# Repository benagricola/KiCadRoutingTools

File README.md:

# KiCad Routing Tools

A fast Rust-accelerated A* autorouter for KiCad PCB files. Compatible with **KiCad 9 and KiCad 10**. Available as both a **KiCad Plugin** with full GUI and a **Command-Line Interface** for scripting and automation.

📊 **[Project metrics](https://drandyhaas.github.io/KiCadRoutingTools/metrics/)** — installs, downloads and traffic, updated daily.

☕ **[Donate](https://ko-fi.com/drandyhaas)** — the tool is free and MIT-licensed; donations cover the ~$500/month of cloud compute and AI development behind it.

## Contents

- [Features](#features)
- [Quick Start](#quick-start)
- [KiCad Plugin](#kicad-plugin) — GUI, the AI **AI tab**, installation
- [Command-Line Interface](#command-line-interface) — routing, planes, verification
- [Documentation](#documentation) — full guide for every feature
- [Project Structure](#project-structure) & [Module Overview](#module-overview)
- [Performance](#performance)
- [Command Reference](#command-reference) — options per tool (full list: `--help` / [configuration.md](docs/configuration.md))
- [Project metrics](https://drandyhaas.github.io/KiCadRoutingTools/metrics/) — installs, downloads and traffic
- [Requirements](#requirements) · [Limitations](#limitations) · [Contributing](#contributing) · [Support](#support) · [License](#license)

## Features

Fast, grid-based A\* routing with a native Rust core (~10× faster than pure Python): octilinear (H/V/45°) multi-layer routing with automatic vias, and batch routing with incremental obstacle caching. Highlights below link to the full deep-dive docs.

**Core routing**
- Rust-accelerated A\* pathfinding, multi-layer with automatic via insertion
- [Rip-up and reroute](docs/rip-up-reroute.md) — progressive N+1 blocker analysis, ripped-corridor avoidance
- [Net ordering strategies](docs/net-ordering.md) — MPS (crossing-aware), inside-out, or original, with MPS layer swaps
- Stub layer switching, vertical track alignment, turn-cost straightening
- Board-edge (Edge.Cuts arcs/cutouts), keep-out rule areas, and auto BGA exclusion zones — see [Configuration](docs/configuration.md)
- Direction-aware stub / BGA / track [proximity penalties](docs/configuration.md)

**Differential pairs** — see [Differential Pairs](docs/differential-pairs.md)
- Pose-based A\* with a Dubins heuristic and adaptive setback angles for orientation-aware centerlines
- Bare-pad, multi-point (3+ terminals), and hybrid (coupled middle + single-ended legs) routing
- Automatic polarity resolution (opt-in pad swaps), U-turn prevention, GND return-via placement
- Electrically-short legs auto-defer to single-ended; per-layer [impedance-controlled](docs/differential-pairs.md) widths

**Power & planes** — see [Plane Routing](docs/route-plane.md) and [Power Nets](docs/power-nets.md)
- [Wider power-net routing](docs/power-nets.md) with automatic neck-down at fine-pitch pads
- Plane pours (pads are welded by the route step, #562) and multi-net Voronoi plane layers with resistance / max-current reporting
- Disconnected-plane-region repair (region joins + pad taps) and GND return-via placement

**Signal integrity**
- [Length matching](docs/length-matching.md) — trombone meanders, auto DQ/DQS grouping, via-barrel aware
- [Time matching](docs/length-matching.md#time-matching) — propagation delay, microstrip vs stripline
- [Bus routing](docs/bus-routing.md), plus [guide corridors and keep-out zones](docs/configuration.md) drawn on a User layer

**Placement, fanout & optimization**
- [Placement optimization](docs/placement-optimization.md) for routability, before routing
- [The design brief](docs/design-brief.md) — state what the board is FOR, in a sibling the toolchain reads: which connectors are user-facing, which edge each belongs on and where along it
- [Floorplan intent, graded](docs/floorplan-intent.md) — declare where parts belong and check the board against it, so "the render looks fine" stops being a verdict
- BGA / QFN fanout with decoupling-cap placement cleanup, Hungarian target-swap, and schematic sync

**Cleanup & verification** — see [Utilities](docs/utilities.md)
- Post-route copper cleanup reconciled against the connectivity model (no orphaned or ripped-and-not-restored copper), with gap-snap connectors
- **KiCad-oracle reconnect** — routes the exact links KiCad's own DRC reports as unconnected
- Checkers for DRC, connectivity, orphan stubs, copper hygiene (`check_weird.py`), and pad geometry

**Interfaces**
- Full [KiCad plugin GUI](#kicad-plugin) (KiCad 9 & 10) and a scriptable [CLI](#command-line-interface)
- [AI assistance](docs/claude-skills.md) — a **AI tab** that plans an entire routing workflow, per-field "Ask AI" helpers, and datasheet-driven power / high-speed / diff-pair analysis
- [Board rendering & routing animation](docs/route-animation.md) — fast geometry PNG renderer, plus a movie of the router laying/ripping/restoring copper (`make_movie.py`, or the Advanced options tab's **Make routing movie** debug checkbox → `.mp4`/`.gif`)
- [Routing plans as files](docs/claude-skills.md#plans-from-the-command-line) — save/load a whole routing chain as JSON: build one from a recorded command chain (`make_plan.py`), run it headless through the real plugin (`run_plan.py`), or load it in the GUI

## Quick Start

### 1. Get the Code

```bash
# Clone with git
git clone https://github.com/drandyhaas/KiCadRoutingTools.git
cd KiCadRoutingTools
```

Or [download the ZIP](https://github.com/drandyhaas/KiCadRoutingTools/archive/refs/heads/main.zip) and extract it.

### 2. Install the Rust Router

```bash
python build_router.py
```

By default this downloads a prebuilt binary for your OS from the project's
[GitHub Releases](https://github.com/drandyhaas/KiCadRoutingTools/releases) —
**no Rust toolchain required**. Prebuilts are published for:

- Linux x86_64
- macOS arm64 (Apple Silicon)
- macOS x86_64 (Intel)
- Windows x86_64

If a prebuilt isn't available for your platform (e.g. Linux arm64) or the
download fails, the script falls back to building locally with cargo.

#### Building from source (optional)

If you'd rather build locally — or you're on a platform without a prebuilt —
install Rust from [rustup.rs](https://rustup.rs/):

```bash
# macOS / Linux
curl --proto '=https' --tlsv1.2 -sSf https://sh.rustup.rs | sh

# Windows: Download and run rustup-init.exe from https://rustup.rs/
```

After installation, restart your terminal or run `source ~/.cargo/env`, then:

```bash
python build_router.py --from-source     # build locally instead of downloading
python build_router.py --tag v0.15.0     # download a specific release
python build_router.py --clean           # remove all build artifacts
```

### 3. Choose Your Interface

**Option A: KiCad Plugin (Recommended for interactive use)**

```bash
# Install the plugin
python install_plugin.py

# Then in KiCad: Tools → External Plugins → KiCadRoutingTools
```

**Option B: Claude Code (AI-assisted routing)**

Use [Claude Code](https://claude.ai/claude-code) to analyze your PCB and generate a routing plan:

```
> /plan-pcb-routing kicad_files/my_board.kicad_pcb
```

Claude will:
- Analyze your board structure and identify components needing fanout (BGA/QFN/PGA)
- Detect differential pairs and DDR signals requiring length matching
- Identify power/ground nets and recommend plane vs trace routing
- Assess signal speeds and recommend GND return via placement
- Generate a step-by-step routing plan with explanations
- Run the commands and verify results

Other useful skills:
```
> /find-high-speed-nets kicad_files/my_board.kicad_pcb       # Identify high-speed nets via datasheet lookup
> /analyze-power-nets kicad_files/my_board.kicad_pcb         # Identify power nets and track widths
> /identify-diff-pairs kicad_files/my_board.kicad_pcb        # Find diff pairs by pin function, recommend gap/impedance
> /recommend-stackup kicad_files/my_board.kicad_pcb          # Stackup advice for impedance/time-matching accuracy
> /diagnose-routing-failures my_board.kicad_pcb /tmp/route_output.txt  # Root-cause failed routes, get a retry command
> /review-routed-board my_board_routed.kicad_pcb             # Post-route QA: DRC, connectivity, length match, GND vias
```

See [Claude Skills](docs/claude-skills.md) for what each skill does and how they fit together.

All of these are also available inside KiCad without leaving the plugin - see [AI assistance in the plugin](#ai-assistance-ai-tab) below. The plugin can run the same skills through [opencode](https://opencode.ai) instead of Claude Code (issue #503) - a Backend dropdown on the AI tab selects the agent CLI, and opencode's `provider/model` strings open the door to other model providers. The skills' output contracts are tuned on Claude models; smaller models may follow them less reliably.

**Option C: Manual Command Line (For scripting and automation)**

```bash
# Optionally optimize an existing placement for routability (before routing)
python py_placer/place_optimize.py my_board.kicad_pcb --max-displacement 3

# Pour the planes FIRST (#562): the fanout's plane-drop vias then land on
# real fill, and the route step welds plane pads into it.
python py_router/route_planes.py my_board.kicad_pcb poured.kicad_pcb --nets GND --plane-layers B.Cu

# Fan out a BGA, then tidy decoupling caps off the new vias (issue #130)
python py_router/bga_fanout.py poured.kicad_pcb -c U1 -o fanned.kicad_pcb --clearance 0.1
python py_placer/place_fanout_clearance.py fanned.kicad_pcb capclean.kicad_pcb --clearance 0.1

# Route differential pairs
python py_router/route_diff.py capclean.kicad_pcb -o diffed.kicad_pcb --nets "*lvds*"

# Route ALL remaining nets, plane nets included (their widths via --power-nets).
# This step ends with the in-run plane finalize that completes the planes.
python py_router/route.py diffed.kicad_pcb routed.kicad_pcb --nets "*" \
    --power-nets GND --power-nets-widths 0.3
```

---

## KiCad Plugin

The plugin provides a full graphical interface for all routing features, running directly within KiCad 9 or 10.

### AI assistance (AI tab)

With [Claude Code](https://claude.ai/claude-code) or [opencode](https://opencode.ai) installed, the routing dialog gains AI assistance throughout (the plugin spawns the selected agent CLI headless, streams a live transcript, and fills GUI controls from the results). The **Backend** dropdown on the AI tab picks the CLI: Claude Code runs Anthropic models; opencode takes `provider/model` strings for many providers (including its built-in free tier), with `opencode auth login` adding provider accounts. Both discover the same `.claude/skills/`; opencode runs them under a read-only `pcb-analysis` agent defined in `opencode.json` (the equivalent of the Claude run's read-only tool allowlist). Neither grants a dedicated write tool, though both grant `Bash`, so neither is a sandbox — the allowlist states intent, and `--allowedTools` auto-approves rather than restricts. They are also not identical: the Claude list grants the subagent-dispatch tool, so an analysis skill there can dispatch an independent verifier (#552), which opencode's pinned agent has no per-run equivalent for. A caller asking opencode for a tool set naming `Write`/`Edit` is refused rather than silently downgraded.

- **AI tab** - *Plan Routing* runs `/plan-pcb-routing`: the plan fills the parameter fields across the tabs and appears as a checkable step list, which *Run Selected Steps* executes sequentially in-process on the live board with per-step status marks. *Review Routed Board* and *Diagnose Routing Failures* give post-route QA and failure root-causing. Backend, model, and effort selectors control every AI run and persist with the dialog settings (model/effort remembered per backend).
- **Save / Load a plan** - *Save…* writes the generated step list to a JSON file; *Load…* reads one back and runs it with **no Claude call** — handy for replaying a workflow that worked on another board. A recorded stress-test chain converts to a loadable plan too (`tests/stress/manifest_to_plan.py <board>/redo_commands.sh plan.json`).
- **Per-field "Ask AI" buttons** - power nets/widths (Route tab), stackup check (Layers), differential-pair verification by pin function (Differential tab), net-to-plane layer mappings and GND return via distance (Planes tab).

The full button-to-skill map is in [Claude Skills - Plugin GUI Integration](docs/claude-skills.md#plugin-gui-integration). Datasheet-based skills use web lookups and take a few minutes; every run shows a live transcript with cancel.

### Installation

Three ways to install:

**A. KiCad Plugin and Content Manager (PCM)** — the recommended path for end users, and it needs no extra repository URL: the package has been in the **official KiCad repository** (the one KiCad ships with, `gitlab.com/kicad/addons`) since v0.15.6. Open the PCM from the KiCad main window, leave the repository dropdown on *KiCad official repository*, go to the **Plugins** tab, search for `routing`, select *KiCad Routing Tools* and click **Install**, then **Apply Changes** at the bottom. If it is not listed, the PCM is serving a cached catalogue — press **Refresh** and look again. Versions are published with status `testing` rather than `stable`, which the PCM shows in the Status column but does not hide or block; `kicad_version` is a *minimum*, so the 9.0 entry installs on KiCad 10 as well. On first launch, the plugin checks the Python packages listed in `requirements.txt` (`numpy`, `scipy`, `shapely`) and offers a one-click pip install for any that are missing **or too old** into KiCad's Python. Do not assume KiCad supplies them: what it bundles varies by version and platform, and KiCad 10 on macOS ships no `numpy` at all. The check reports the version and the file path the *running* interpreter imports — KiCad's Python is often not the one `pip show numpy` answers for in a terminal.

**B. PCM "Install from File…" using the release zip** — for a release newer than the one the official catalogue currently carries, for a pinned older version, or for an offline machine. Each [GitHub Release](https://github.com/drandyhaas/KiCadRoutingTools/releases) ships a ready-to-install PCM package zip named `KiCadRoutingTools-<version>.zip` (a single cross-platform archive bundling the prebuilt Rust binaries for all platforms — **not** the auto-generated "Source code (zip)"). To install it:

1. From the Release's *Assets*, download `KiCadRoutingTools-<version>.zip` (e.g. `KiCadRoutingTools-0.15.13.zip`).
2. In KiCad, open **Plugin and Content Manager** from the main window.
3. Click **Install from File…** (bottom of the PCM dialog) and select the downloaded zip.
4. Click **Apply Pending Changes**, then restart KiCad if prompted.

The plugin appears under *Tools → External Plugins* in the PCB Editor. The same first-launch `scipy`/`shapely` dependency check described in (A) applies. This path keeps the plugin manageable from the PCM (you can update or uninstall it there), unlike the manual install below.

**C. Manual install from source** — for development or for using the CLI tools as well:

```bash
# Install the plugin (copies to KiCad plugins directory)
python install_plugin.py

# For development: create symlink instead of copying
python install_plugin.py --symlink

# Remove the plugin
python install_plugin.py --uninstall
```

The installer automatically detects your KiCad installation directory (supports KiCad 9.0 and 10.0):
- **macOS**: `~/Documents/KiCad/<version>/3rdparty/plugins/`
- **Linux**: `~/.local/share/kicad/<version>/3rdparty/plugins/`
- **Windows**: `~/Documents/KiCad/<version>/3rdparty/plugins/`

The installer also installs `requirements.txt` into KiCad's Python with pip, and skips pip when that Python already has everything. On Linux, KiCad runs the system Python, which Debian 12+, Ubuntu 23.04+, Fedora 38+ and Arch mark as externally managed (PEP 668) so pip refuses to install into it; there the installer runs no pip and prints the `apt` / `dnf` / `pacman` command for whatever is missing, plus the explicit `--break-system-packages` override for a package your distribution does not carry.

If you previously installed this plugin through the Plugin & Content Manager, that copy sits next to the local install and would shadow it on `sys.path` (causing stale-code errors). The installer detects any such PCM copy and moves it aside to `<kicad-base>/disabled_pcm_plugins/<version>/`, leaving it recoverable. Pass `--keep-pcm` to skip this.

### Releasing a new version (maintainers)

The full release flow — version bump, GitHub Release, and the merge request to the official KiCad PCM repository — is documented step by step in **[docs/release-pipeline.md](docs/release-pipeline.md)**.

Short version:

1. Bump `VERSION` and the `versions[]` entry in `metadata.json`.
2. `git tag v0.15.6 && git push --tags` — CI builds all 4 platform binaries, packages a single `KiCadRoutingTools-<ver>.zip` (the PCM validator rejects duplicate version strings, so we ship one cross-platform zip), patches `metadata.json` with real sha256/size values, and attaches everything to the GitHub Release.
3. Append the new version to the metadata file in your fork of `gitlab.com/kicad/addons/metadata` and open an MR. See the docs page for the exact commands.

To build a zip locally for testing:

```bash
python package_pcm.py --binary-dir ./path/to/release/artifacts
```

### Usage

1. Open KiCad (9.0 or later)
2. Open a PCB in Pcbnew
3. *(Optional)* Select one or more nets in the PCB editor first — for example by
   clicking tracks/pads, or right-clicking a track and choosing
   **Select → All Tracks in Net**. Any nets you have selected are automatically
   pre-checked for routing when the plugin opens.
4. Go to **Tools → External Plugins → KiCadRoutingTools**
5. Configure routing parameters and select (or adjust) the nets to route
6. Click **Route** to run the router

### Plugin Tabs

**Route Tab:**
- Net selection with filtering and component filtering
- Nets selected in the PCB editor before opening the plugin are pre-checked automatically (also applies to the Fanout, Planes, and Differential tabs)
- Option to separate nets by net class (organizes into tabs per class)
- Track width, clearance, via size/drill from net class or manual override
- Layer selection with per-layer cost multipliers
- Options: stub layer swaps, copper text moving, teardrops, power net widths, no-BGA zones
- **Guide corridor** - draw a polyline on a User layer (e.g. `User.1`) and tick "Follow User-layer guide path" to route the selected nets along it (waypoints, avoiding obstacles, packed non-overlapping)
- **Keepout zones** - draw one or more closed polygons on a User layer (e.g. `User.2`) and tick "Keep out of User-layer polygon(s)" to keep routed tracks out of those areas (hard keepout, all routed nets)
- **Clear guide/keepout layers** - optional "Clear guide layer after routing" / "Clear keepout layer after routing" checkboxes (unchecked by default) delete the drawn guide/keepout graphics from their User layer after a successful route, so you can draw fresh ones for the next run

**Advanced options Tab:**
- Swappable nets configuration for target swap optimization
- Routing parameters: iterations, heuristic weight, rip-up, probe iterations
- MPS ordering options, direction control, length matching
- Proximity settings: BGA, stub, track, via proximity costs
- Debug options

**Differential Tab:**
- Differential pair selection with filtering
- Pair gap, turning radius, setback angle configuration
- Options: polarity fix, GND vias, intra-pair length matching

**Fanout Tab:**
- BGA fanout with exit margin, escape direction, differential pair support
- Under-pad escape option for dense, fully-populated BGAs the channel router can't escape (issue #122) — see [BGA Fanout](py_router/bga_fanout/README.md#escape-methods)
- "Optimize decoupling cap placement" option (off by default) — after fanout, nudges decoupling caps off foreign-net fanout vias and toward same-net balls (issue #130) — see [Placement](py_placer/placement/README.md#place_fanout_clearancepy--decoupling-cap-clearance-repair-issue-130)
- QFN fanout with extension length configuration
- Net selection for fanout operations

**Planes Tab** (pour creation only since #562 — plane repair runs inside
every route, and the route step welds plane pads into the pour):
- Net-to-layer assignment for power/ground planes
- Create the pours (plus thermal via arrays under exposed pads)
- Area via stitching and GND return via placement near signal vias
- Via size/drill, zone clearance configuration

**Log Tab:**
- Real-time routing output display
- Color-coded messages (errors, warnings, success)

**About Tab:**
- Version information and credits

**General Features:**
- Settings persistence (parameters and selections preserved between sessions)
- Cancel button to stop routing operations mid-progress
- Results applied directly to the open PCB in KiCad

---

## Command-Line Interface

### Net Pattern Syntax

All `--nets` options support fnmatch-style wildcards and exclusion patterns:

| Pattern | Description |
|---------|-------------|
| `*` | All nets |
| `*DATA*` | Nets containing "DATA" |
| `/*` | Nets starting with "/" (hierarchical) |
| `Net-(U1-*)` | Nets matching "Net-(U1-...)" |
| `!GND` | Exclude net named "GND" |
| `!*VCC*` | Exclude nets containing "VCC" |
| `"*" "!GND" "!VCC"` | All nets except GND and VCC |

**Notes:**
- Exclusion patterns (starting with `!`) remove matching nets from the result
- Order matters: include patterns add nets, exclude patterns remove them
- Nets starting with "unconnected-" are automatically excluded
- Use quotes around patterns with special characters

### Route Nets

```bash
# Route all nets (default) - outputs to input_routed.kicad_pcb
python py_router/route.py kicad_files/input.kicad_pcb

# Route all nets, overwrite input file
python py_router/route.py kicad_files/input.kicad_pcb --overwrite

# Route all nets to a specific output file
python py_router/route.py kicad_files/input.kicad_pcb kicad_files/output.kicad_pcb

# Route specific nets (using --nets option)
python py_router/route.py kicad_files/input.kicad_pcb kicad_files/output.kicad_pcb --nets "Net-(U2A-DATA_0)" "Net-(U2A-DATA_1)"

# Route with wildcard patterns
python py_router/route.py kicad_files/input.kicad_pcb kicad_files/output.kicad_pcb --nets "Net-(U2A-DATA_*)"

# Route all nets on a component (auto-excludes GND/VCC/VDD/unconnected)
python py_router/route.py kicad_files/input.kicad_pcb kicad_files/output.kicad_pcb --component U1

# Route specific patterns on a component (no auto-exclusion)
python py_router/route.py kicad_files/input.kicad_pcb kicad_files/output.kicad_pcb --nets "/DDAT*" --component U1

# Route ALL nets on a component including power (use "*" pattern)
python py_router/route.py kicad_files/input.kicad_pcb kicad_files/output.kicad_pcb --nets "*" --component U1

# Exclusion-pattern SYNTAX demo (! prefix). NOTE: in the #562 chain you do
# NOT exclude plane nets from the route step -- see the chain example below.
python py_router/route.py kicad_files/input.kicad_pcb kicad_files/output.kicad_pcb --nets "*" "!GND" "!VCC"

# Route one placement BLOCK -- a schematic sheet, a KiCad group, an IC and its decaps
# (see "Placement blocks" below for what --group-by can infer, and --list-groups)
python py_router/route.py kicad_files/input.kicad_pcb kicad_files/output.kicad_pcb \
  --group-by sheet --list-groups                      # what blocks exist?
python py_router/route.py kicad_files/input.kicad_pcb kicad_files/output.kicad_pcb \
  --group sheet:558c3023 --group-by sheet --group-scope internal

# PREVIEW any routing run: route it, report what it WOULD add, write no board
python py_router/route.py kicad_files/input.kicad_pcb kicad_files/output.kicad_pcb \
  --group sheet:558c3023 --group-by sheet --preview --preview-png preview.png

# UNDO: strip the scoped nets' copper back to unrouted (needs an explicit scope;
# defaults to --group-scope internal, since a block's "touching" nets include
# GND/VCC and undoing those would strip their copper across the whole board)
python py_router/route.py kicad_files/input.kicad_pcb kicad_files/undone.kicad_pcb \
  --group sheet:558c3023 --group-by sheet --undo

# Route differential pairs (use route_diff.py)
python py_router/route_diff.py kicad_files/input.kicad_pcb kicad_files/output.kicad_pcb --nets "*lvds*" --no-bga-zones

# Route with wider tracks for power nets
python py_router/route.py kicad_files/input.kicad_pcb kicad_files/output.kicad_pcb --nets "Net*" \
  --power-nets "*GND*" "*VCC*" "+3.3V" --power-nets-widths 0.4 0.5 0.3 --track-width 0.2

# Grid alignment is on by default: the board is routed translated by the
# sub-grid offset that puts the most fine-pitch pin rows on the routing grid,
# and the result translated back (docs/off-grid-exact-fit-design.md). To route
# the board where it is:
python py_router/route.py kicad_files/input.kicad_pcb kicad_files/output.kicad_pcb --no-align-grid

# Typical workflow: create GND plane first, then route all signals
python py_router/route_planes.py kicad_files/flat_hierarchy.kicad_pcb --nets GND --plane-layers B.Cu
python py_router/route.py kicad_files/flat_hierarchy_routed.kicad_pcb --overwrite
```

### 3. Create Power/Ground Planes

```bash
# Create GND zone on B.Cu with via connections to all GND pads (outputs to input_routed.kicad_pcb)
python py_router/route_planes.py kicad_files/input.kicad_pcb --nets GND --plane-layers B.Cu

# Create GND zone, overwrite input file
python py_router/route_planes.py kicad_files/input.kicad_pcb --overwrite --nets GND --plane-layers B.Cu

# Create GND zone to specific output file
python py_router/route_planes.py kicad_files/input.kicad_pcb kicad_files/output.kicad_pcb --nets GND --plane-layers B.Cu

# Create multiple planes at once (each net paired with corresponding plane layer)
python py_router/route_planes.py kicad_files/input.kicad_pcb --nets GND +3.3V --plane-layers In1.Cu In2.Cu

# Create VCC plane with larger vias
python py_router/route_planes.py kicad_files/input.kicad_pcb --nets VCC --plane-layers In2.Cu --via-size 0.5 --via-drill 0.4

# Pour planes (the pour places no taps: the route step welds plane pads)
python py_router/route_planes.py kicad_files/input.kicad_pcb --nets GND +3.3V --plane-layers In1.Cu In2.Cu

# Multiple nets sharing same layer via Voronoi partitioning (use | separator)
python py_router/route_planes.py kicad_files/input.kicad_pcb --nets GND "VA19|VA11" --plane-layers In4.Cu In5.Cu

# Dry run to see what would be placed
python py_router/route_planes.py kicad_files/input.kicad_pcb --nets GND --plane-layers B.Cu --dry-run
```

### 3b. Repair Disconnected Plane Regions

> **Since #562 you normally do not run this step.** Every `route.py` run
> finishes with an in-run *plane finalize* that applies this same engine
> (pad taps + region joins), the plane-copper cleanup, and a KiCad-oracle
> completion check — so a pours-first chain repairs its planes automatically.
> `KICAD_PLANE_FINALIZE=0` is the kill switch. Use the standalone script
> below for a board routed OUTSIDE that chain (e.g. hand-edited copper).

After creating power planes, regions may become split by vias and traces from other nets. Use `repair_planes.py` to reconnect them:

```bash
# Auto-detect all zones in PCB and repair disconnected regions (outputs to input_routed.kicad_pcb)
python py_router/repair_planes.py kicad_files/input.kicad_pcb

# Auto-detect all zones, overwrite input
python py_router/repair_planes.py kicad_files/input.kicad_pcb --overwrite

# Auto-detect all zones to specific output file
python py_router/repair_planes.py kicad_files/input.kicad_pcb kicad_files/output.kicad_pcb

# Specific nets and layers
python py_router/repair_planes.py kicad_files/input.kicad_pcb --nets GND --plane-layers B.Cu

# Customize track width and clearance
python py_router/repair_planes.py kicad_files/input.kicad_pcb kicad_files/output.kicad_pcb \
    --track-width 0.5 --clearance 0.2
```

### 3c. Review a Placement (issue #431)

Placement deltas are invisible in a board file; render them instead.

```bash
# what moved, and did it help? (ghosts at the seed poses, arrows, metrics caption)
python3 py_tools/render_placement.py placed.kicad_pcb --before seed.kicad_pcb -o delta.png

# zoom to one placement block; same block names as route.py --group
python3 py_tools/render_placement.py board.kicad_pcb --list-groups --group-by sheet
python3 py_tools/render_placement.py board.kicad_pcb --zoom-group sheet:58d913ec --per-side -o out/

# which parts should NOT be moved -- advice only, locks nothing, writes no board
python3 py_placer/place_optimize.py board.kicad_pcb --suggest-locks
```

Toggles for `--borders` / `--labels` / `--ratsnest` / `--arrows` / `--ghosts`;
`--per-side` gives F and B panels rather than one flattened projection.
The render is triage -- the verdict is the caption's `crossings` / `hpwl`.

### 4. Verify Results

```bash
# Check for DRC violations. With no -c, grades at the clearance the routing
# steps wrote into the sibling .kicad_pro (the smallest clearance any step
# actually used); falls back to 0.2mm if there's no project. Pass -c to override.
python py_router/check_drc.py kicad_files/output.kicad_pcb

# Cross-check with KiCad's own DRC engine (requires KiCad; --refill-zones avoids
# bogus zone-clearance errors from stale pours - see tests/README.md for details)
kicad-cli pcb drc --refill-zones --format json -o drc.json kicad_files/output.kicad_pcb

# ...because a routed board ships zone OUTLINES with no filled_polygon, so an
# unrefilled grade reports plane opens that are not real (#910). To ship a
# board that already carries its fills, add --write-fill to the route step, or:
python py_tools/fill_for_delivery.py kicad_files/output.kicad_pcb -o delivered.kicad_pcb

# Check connectivity (detects unrouted nets, broken routes, and T-junctions)
python py_router/check_connected.py kicad_files/output.kicad_pcb

# Check connectivity for specific nets
python py_router/check_connected.py kicad_files/output.kicad_pcb --nets "*DATA*"

# Check connectivity for all nets on a component
python py_router/check_connected.py kicad_files/output.kicad_pcb --component U1

# Only check routed nets (skip unrouted net detection)
python py_router/check_connected.py kicad_files/output.kicad_pcb --routed-only

# Check for orphan stubs (dead-end traces with no pad/via/trace at the loose end).
# Connection is judged by actual copper extent (via radius, pad size, trace
# half-width), so T-junction taps and copper-overlap joints are not miscounted.
python py_tools/check_orphan_stubs.py kicad_files/output.kicad_pcb

# Pad-geometry sanity check: flags same-footprint, different-net pads whose copper
# overlaps (a short). A non-zero result almost always means a pad's rotation/size
# is modelled wrong - the usual cause is a QFN/QFP/BGA placed at a non-orthogonal
# angle. The fanout tools run this automatically on their component first; run it
# yourself before fanout (or board-wide) as a standalone check:
python py_router/check_pads.py kicad_files/board.kicad_pcb                 # whole board, per footprint
python py_router/check_pads.py kicad_files/board.kicad_pcb --component U23 # one footprint
python py_router/check_pads.py kicad_files/board.kicad_pcb --cross-footprint  # also across parts

# Flag long non-orthonormal tracks. An on-grid router emits only 0/45/90-degree
# segments; the only legitimate non-orthonormal segment is a short (<=1 grid cell)
# terminal connector to an off-grid pad/ball. Anything longer is a routing defect
# (it can cut diagonally across foreign copper). qfn_fanout escape stubs are
# excluded automatically; bga_fanout's short stub-end jogs clear the 0.25mm default.
python py_tools/check_orthonormal.py kicad_files/output.kicad_pcb

# Copper hygiene (read-only): dangling stubs, same-net soft joints, redundant
# cycles, and removable / stacked / floating copper the routing left behind.
python py_router/check_weird.py kicad_files/output.kicad_pcb
```

See [Utilities](docs/utilities.md) for every checker and its options.

### 5. Power Net Analysis

Use the `/analyze-power-nets` skill to identify power nets and get track width recommendations:

```
# Ask the AI to analyze your board with datasheet lookup
/analyze-power-nets kicad_files/my_board.kicad_pcb
```

The skill:
1. Auto-classifies obvious components (resistors, capacitors, inductors, etc.)
2. Uses WebSearch to look up datasheets for unknown components (ICs, connectors, transistors)
3. Classifies each component's role (power source, current sink, pass-through, shunt)
4. Traces power paths from sinks to sources
5. Generates ready-to-use `--power-nets` configurations

See [Power Net Analysis](docs/power-nets.md) for detailed documentation.

### 6. High-Speed Net Analysis

Use the `/find-high-speed-nets` skill to identify high-speed nets and get GND return via recommendations:

```
# Ask the AI to analyze signal speeds with datasheet lookup
/find-high-speed-nets kicad_files/my_board.kicad_pcb
```

The skill:
1. Pre-classifies nets by name patterns (DDR, USB, SPI, CLK, etc.)
2. Pre-classifies components by footprint (FPGA, DDR, PHY, etc.)
3. Uses WebSearch to look up datasheets for ICs and extract max clock rates and rise times
4. Traces high-speed signals through series passives (termination resistors, AC coupling caps)
5. Generates a speed classification (ultra-high/high/medium/low) with recommended `--gnd-via-distance`

The `/plan-pcb-routing` skill includes a lightweight version of this analysis (net name and
footprint pattern matching only, no datasheet lookup) and automatically includes a GND return
via step when GND planes are present. Run `/find-high-speed-nets` first for more accurate
recommendations based on actual component specifications.

### 7. Integration Tests

```bash
# Run full integration test (fanout + routing + checks)
python tests/test_fanout_and_route.py --all

# Quick mode for faster testing
python tests/test_fanout_and_route.py --all --quick
```

See [tests/README.md](tests/README.md) for detailed documentation of all test scripts.

## Documentation

| Document | Description |
|----------|-------------|
| [Routing Architecture](docs/routing-architecture.md) | Module structure, obstacle maps, A* algorithm |
| [Python API](docs/python-api.md) | Using the modules as a library: parser, writer, modification, config, net analysis, impedance — with runnable examples |
| [Configuration](docs/configuration.md) | Command-line options, GridRouteConfig parameters |
| [Differential Pairs](docs/differential-pairs.md) | P/N pairing, polarity swaps, via handling |
| [Net Ordering](docs/net-ordering.md) | MPS algorithm, inside-out ordering, strategy comparison |
| [Rip-Up and Reroute](docs/rip-up-reroute.md) | Blocking analysis, progressive N+1 escalation, reroute loop |
| [Length Matching](docs/length-matching.md) | Trombone meanders, via barrel lengths, DDR auto-grouping, time matching |
| [Bus Routing](docs/bus-routing.md) | Bus detection, middle-out ordering, neighbor attraction |
| [Guide Corridor](docs/configuration.md#guide-corridor-options-preferred-route) | User-layer guide paths, waypoints, best-effort following |
| [Power/Ground Planes](docs/route-plane.md) | Copper zones with automatic via placement |
| [Utilities](docs/utilities.md) | DRC checker, connectivity checker, fanout generators, layer switcher, DRC-settings fixer |
| [Design Brief](docs/design-brief.md) | Declare what the board IS -- the facts a board file cannot contain -- and compile them into the intent (`<board>.design-brief.json`) |
| [Floorplan Intent](docs/floorplan-intent.md) | Declare the floorplan, grade the board against it (`check_floorplan.py`) |
| [Placement Predictors](docs/placement-predictors.md) | What actually predicts routed `blocking`, measured (#703) |
| [Placement Calibration](docs/placement-calibration.md) | Why P-close's routability threshold was withdrawn, and the rows it was withdrawn on (#803) |
| [BGA Fanout](py_router/bga_fanout/README.md) | BGA escape routing generator |
| [QFN Fanout](py_router/qfn_fanout/README.md) | QFN/QFP escape routing generator |
| [Rust Router](rust_router/README.md) | Building and using the Rust A* module |
| [Power Net Analysis](docs/power-nets.md) | Power net detection, AI analysis, track width guidelines |
| [Claude Skills](docs/claude-skills.md) | All nine AI skills: routing plans, power/high-speed/diff-pair analysis, stackup, plane mappings, failure diagnosis, board review |
| [Placement](py_placer/placement/README.md) | Placement optimization for routability |
| [Integration Tests](tests/README.md) | Test scripts and performance benchmarks |
| [Release Pipeline](docs/release-pipeline.md) | How to tag a release and submit it to the KiCad PCM (maintainers) |

## Project Structure

```
KiCadRoutingTools/
├── py_router/                # Routing engine + CLI entry points (~100 modules)
│   ├── place_optimize.py         # Main CLI - placement optimization (quench)
│   ├── place_route_loop.py       # Main CLI - router-in-the-loop placement repair
│   ├── route.py                  # Main CLI - single-ended routing (ends with the in-run plane finalize, #562)
│   ├── route_diff.py             # Main CLI - differential pair routing
│   ├── route_planes.py           # Main CLI - power/ground plane pours
│   ├── repair_planes.py          # Standalone utility - repair disconnected plane regions (the chain step is absorbed into route.py's finalize, #562)
│   ├── plane_io.py               # Plane I/O utilities (zone extraction, output writing)
│   ├── plane_obstacle_builder.py # Obstacle map building for plane via placement
│   ├── plane_blocker_detection.py # Blocker detection and rip-up for plane vias
│   ├── plane_zone_geometry.py    # Voronoi zone computation for multi-net layers
│   ├── plane_resistance.py       # Plane resistance and current capacity calculations
│   ├── plane_region_connector.py # Detect and route between disconnected plane regions
│   ├── routing_config.py         # GridRouteConfig, GridCoord, DiffPair classes
│   ├── routing_defaults.py       # Default routing parameter values
│   ├── routing_state.py          # RoutingState class - tracks routing progress
│   ├── routing_common.py         # Shared utilities for route.py and route_diff.py
│   ├── obstacle_map.py           # Obstacle map building functions
│   ├── obstacle_cache.py         # Net obstacle caching for incremental builds
│   ├── diff_pair_loop.py         # Differential pair routing loop
│   ├── single_ended_loop.py      # Single-ended routing loop
│   ├── reroute_loop.py           # Reroute queue processing
│   ├── diff_pair_routing.py      # Diff pair A* routing implementation
│   ├── single_ended_routing.py   # Single-ended A* routing implementation
│   ├── net_ordering.py           # MPS, inside-out, and original ordering
│   ├── rip_up_reroute.py         # Rip-up and reroute logic
│   ├── length_matching.py        # Length matching with trombone meanders
│   ├── kicad_parser.py           # KiCad .kicad_pcb file parser
│   ├── kicad_writer.py           # KiCad S-expression generator
│   ├── output_writer.py          # Route output and swap application
│   ├── pcb_modification.py       # Add/remove routes from PCB data
│   ├── impedance.py              # Impedance calculation (microstrip/stripline formulas)
│   ├── check_drc.py              # DRC violation checker
│   ├── check_connected.py        # Connectivity checker (with T-junction detection)
│   ├── check_pads.py             # Pad-geometry sanity checker
│   ├── check_weird.py            # Copper hygiene checker
│   ├── fix_kicad_drc_settings.py # Make .kicad_pro DRC constraints consistent with the routed floors
│   ├── copy_board.py             # Copy a board WITH its sibling .kicad_pro/.kicad_dru
│   ├── list_nets.py              # List nets on a component
│   ├── startup_checks.py         # Startup checks (Python deps, Rust library version)
│   ├── bga_fanout.py             # BGA fanout CLI wrapper
│   ├── bga_fanout/               # BGA fanout package (escape, reroute, layer balance, under-pad escape, ...)
│   ├── qfn_fanout.py             # QFN/QFP fanout CLI wrapper
│   ├── qfn_fanout/               # QFN/QFP fanout package (layout, geometry, types)
│   ├── placement/                # Component placement package
│   │   ├── quench.py             # Placement optimizer
│   │   ├── fanout_clearance.py   # Fanout clearance evaluation
│   │   ├── parser.py             # Courtyard boundary extraction
│   │   ├── writer.py             # Footprint position modification
│   │   ├── groups.py             # Group-move support
│   │   ├── body.py               # THE footprint body model (#896)
│   │   ├── legality.py           # Placement legality checks
│   │   └── utility.py            # Shared placement utilities
│   └── ...                       # plus the rest of the engine modules — see Module Overview below
│
├── py_tools/                 # Leaf diagnostic / analysis tools
│   ├── check_impedance.py        # Verify impedance-controlled widths/gaps
│   ├── check_orphan_stubs.py     # Orphan stub detector
│   ├── check_cycles.py           # Redundant-loop (cycle) + overlapping-via checker
│   ├── check_orthonormal.py      # Long non-orthonormal track detector
│   ├── net_forensics.py          # Per-net copper forensics
│   ├── kicad_unconnected.py      # Unconnected-item listing
│   ├── validate_pcb_data.py      # PCBData validation
│   ├── extract_pcb_geometry.py   # Geometry extraction
│   ├── clean_ignored.py          # Remove ignored copper
│   ├── analyze_power_paths.py    # Power-path analysis (backs /analyze-power-nets)
│   ├── animate_fanout_clearance.py # Animate cap-placement repair
│   └── _path.py                  # sys.path bootstrap so the tools import py_router
│
├── tests/                    # Integration tests
│   ├── test_fanout_and_route.py  # Full integration test (fanout + route)
│   ├── test_kit_route.py         # Pad-to-pad routing test (no fanout)
│   ├── test_flat_hierarchy.py    # 2-layer board with GND plane test
│   ├── test_interf_u.py          # 2-layer board with non-rectangular outline test
│   ├── test_sonde_u.py           # Wide track routing test
│   ├── run_utils.py              # Shared test utilities
│   ├── gui_parity/               # CLI/GUI parity gates — see tests/gui_parity/README.md
│   └── stress/                   # Real-world-board stress-test harness (run_queue.sh) — see tests/README.md
│
├── rust_router/              # Rust A* implementation
├── kicad_routing_plugin/     # KiCad ActionPlugin
│   ├── action_plugin.py      # ActionPlugin entry point
│   ├── swig_gui.py           # Main routing dialog (Route/Advanced options tabs)
│   ├── differential_gui.py   # Differential pair routing tab
│   ├── fanout_gui.py         # BGA/QFN fanout tab and net selection panel
│   ├── planes_gui.py         # Power/ground planes tab
│   ├── ai_gui.py             # AI tab (spawns the agent CLI headless, streams transcript)
│   ├── ai_plan.py            # AI tab routing-plan orchestration
│   ├── ai_backend.py         # Agent CLI backend selection (Claude Code / opencode)
│   ├── movie_recorder.py     # Routing-movie capture for the GUI
│   ├── board_swaps.py        # Shared board pad/net swap helpers
│   ├── deps_check.py         # Plugin dependency checks
│   ├── about_tab.py          # About tab with version info
│   ├── gui_utils.py          # Shared GUI utilities
│   └── settings_persistence.py  # Save/restore dialog settings between sessions
├── build_router.py           # Rust module build script (--clean to remove artifacts)
├── install_plugin.py         # Plugin installer script
├── kicad_files/              # Example and test boards
├── docs/                     # Documentation
└── .claude/skills/           # Claude Code skills
    ├── analyze-power-nets/   # AI-powered power net analysis skill
    ├── find-high-speed-nets/ # AI-powered high-speed net identification skill
    ├── plan-pcb-routing/     # AI-powered routing plan generation skill (orchestrates the others)
    ├── identify-diff-pairs/  # Datasheet-based diff pair detection skill
    ├── recommend-stackup/    # Stackup review/recommendation skill
    ├── recommend-plane-mappings/  # Net-to-plane-layer assignment skill
    ├── diagnose-routing-failures/  # Failure root-cause and retry skill
    ├── review-routed-board/  # Post-route QA and sign-off skill
    └── stress-test-router/   # Batch stress-test on real-world boards + issue filing (dev/QA)
```

## Module Overview

One-line summaries below (all of these modules live in `py_router/`); the
[Python API documentation](docs/python-api.md) has full per-module references
(signatures, dataclass fields, gotchas) with runnable examples.

### Core Routing

| Module | Purpose |
|--------|---------|
| `route.py` | CLI for single-ended routing |
| `route_diff.py` | CLI for differential pair routing |
| `route_planes.py` | CLI for power/ground plane via connections |
| `repair_planes.py` | CLI for repairing disconnected plane regions |
| `routing_config.py` | Configuration dataclasses (`GridRouteConfig`, `GridCoord`, `DiffPair`) |
| `routing_state.py` | `RoutingState` class tracking progress, results, and PCB modifications |
| `routing_context.py` | Helper functions for building obstacles and recording success |
| `routing_common.py` | Shared utilities for route.py and route_diff.py (BGA zones, net resolution, length matching) |
| `routing_utils.py` | Shared utilities (`build_layer_map`, `iter_pad_blocked_cells`) |
| `obstacle_map.py` | Obstacle map building from PCB data |
| `obstacle_cache.py` | Net obstacle caching for incremental obstacle map builds |
| `obstacle_costs.py` | Stub and track proximity cost calculations |
| `bresenham_utils.py` | Bresenham line-walking utilities for grid-based segment operations |
| `geometry_utils.py` | Shared geometry calculations (point-to-segment distance, segment intersection, UnionFind) |
| `routing_constants.py` | Shared constants (default layer stack, power net patterns, tolerances) |
| `terminal_colors.py` | ANSI color codes for terminal output |

### Routing Loops

| Module | Purpose |
|--------|---------|
| `diff_pair_loop.py` | Main loop for routing differential pairs |
| `single_ended_loop.py` | Main loop for routing single-ended nets |
| `reroute_loop.py` | Processes reroute queue for failed routes |
| `phase3_routing.py` | Phase 3 multi-point tap routing (connects remaining pads after length matching) |
| `diff_pair_routing.py` | Differential pair A* with centerline + offset and GND vias |
| `single_ended_routing.py` | Single-ended net A* routing |

### Net Analysis

| Module | Purpose |
|--------|---------|
| `net_ordering.py` | MPS, inside-out, and original net ordering strategies |
| `net_queries.py` | Net queries (diff pair detection, MPS ordering, power net detection, chip pad positions) |
| `connectivity.py` | Stub endpoints, connected groups, multi-point net detection |

Key functions in `net_queries.py`:
- `identify_power_nets(pcb, patterns, widths)` - Pattern-based power net detection for `--power-nets` CLI option
- `compute_mps_net_ordering(pcb, net_ids)` - MPS algorithm for optimal net ordering
- `find_differential_pairs(pcb, patterns)` - Detect P/N pairs from net names (suffix-style aware: `+`/`-` nets only pair with each other, never with `_P`/`_N` nets sharing the same base name)

Key functions in `py_tools/analyze_power_paths.py` (used by `/analyze-power-nets` skill):
- `analyze_pcb(filepath)` - Load PCB and extract components for analysis
- `get_components_needing_analysis(components)` - Get components requiring AI classification
- `classify_component(components, ref, role, current_ma, notes)` - Set component classification
- `trace_power_paths(pcb, components)` - Trace current from sinks to sources
- `get_power_net_recommendations(pcb, components, paths)` - Get recommended track widths

### Optimization

| Module | Purpose |
|--------|---------|
| `layer_swap_optimization.py` | Upfront layer swap optimization before routing |
| `layer_swap_fallback.py` | Try layer swap when route fails |
| `stub_layer_switching.py` | Low-level stub layer swap utilities |
| `mps_layer_swap.py` | MPS-aware layer swap for crossing conflicts |
| `polarity_swap.py` | P/N polarity swap for differential pairs |
| `target_swap.py` | Hungarian algorithm for optimal target assignment |
| `rip_up_reroute.py` | Rip-up blocking routes and retry |
| `blocking_analysis.py` | Analyze which nets are blocking |
| `length_matching.py` | Length matching with trombone-style meanders |

### I/O and Utilities

| Module | Purpose |
|--------|---------|
| `kicad_parser.py` | KiCad .kicad_pcb file parser (extracts stackup, footprint values, pintypes) |
| `kicad_writer.py` | KiCad S-expression generator |
| `output_writer.py` | Write routed output with swaps and debug geometry |
| `pcb_modification.py` | Add/remove routes from PCB data structure |
| `schematic_updater.py` | Update .kicad_sch files with pad swaps from routing |
| `impedance.py` | Impedance calculations (microstrip/stripline, width from target Z) |
| `memory_debug.py` | Memory usage statistics and debugging |

## Performance

Integration test results (`tests/test_fanout_and_route.py`):

| Stage | Nets | Time | Iterations |
|-------|------|------|------------|
| FTDI single-ended | 47/47 | 8.6s | 319K |
| LVDS diff pairs (batch 1) | 28/28 | 29.7s | 10.2M |
| LVDS diff pairs (batch 2) | 28/28 | 28.0s | 12.0M |
| DDR diff pairs | 5/5 | 0.3s | 25K |
| DDR single-ended | 51/51 | 6.2s | 565K |

Rust acceleration provides ~10x speedup vs pure Python.

## Command Reference

Every tool prints its full option list with `--help`, and **[docs/configuration.md](docs/configuration.md)** is the single source of truth for the flags — defaults, guidance, and which tool each applies to. The tool-specific guides go deeper on their area:

| Tool | Purpose | Guide |
|------|---------|-------|
| `route.py` | Single-ended routing | [Configuration](docs/configuration.md) |
| `route_diff.py` | Differential-pair routing | [Differential Pairs](docs/differential-pairs.md) |
| `route_planes.py` | Power/ground plane via connections | [Plane Routing](docs/route-plane.md) |
| `repair_planes.py` | Plane region repair + pad taps | [Plane Routing](docs/route-plane.md) |
| `bga_fanout.py` / `qfn_fanout.py` | BGA / QFN escape fanout | [BGA](py_router/bga_fanout/README.md) · [QFN](py_router/qfn_fanout/README.md) · [Utilities](docs/utilities.md) |
| `place_fanout_clearance.py` | Move decoupling caps off fanout vias | [Utilities](docs/utilities.md) |
| `place_optimize.py` | Placement for routability | [Placement Optimization](docs/placement-optimization.md) |
| `board_brief.py` | Assemble what a placement author needs to read, in one artifact | [Design Brief](docs/design-brief.md) |
| `check_floorplan.py` | Grade a board against a declared floorplan intent | [Floorplan Intent](docs/floorplan-intent.md) |
| `check_*.py` | DRC / connectivity / hygiene / pad checks | [Utilities](docs/utilities.md) |
| `make_movie.py` | Movie of a routing run (`.mp4`/`.gif`) | [Rendering & animation](docs/route-animation.md) |
| `make_plan.py` / `run_plan.py` | Build a GUI routing plan from a recorded chain / run one headless | [Plans from the CLI](docs/claude-skills.md#plans-from-the-command-line) |

```bash
# Full option list for any tool
python py_router/route.py --help

# A typical chain (#562 pours-first): pour, then diff pairs, then ONE route
# over ALL nets -- plane nets INCLUDED. The pour places no taps; the route
# step welds plane pads into the fill and its in-run finalize completes them,
# so do NOT exclude the plane nets here.
python py_router/route_planes.py board.kicad_pcb board.kicad_pcb --nets GND --plane-layers B.Cu
python py_router/route_diff.py board.kicad_pcb -O --nets "*_P" "*_N" --diff-pair-gap 0.15
python py_router/route.py board.kicad_pcb -O --nets "*" --power-nets GND --power-nets-widths 0.3
```

The shared option groups — geometry, power-net widths, algorithm/strategy, proximity penalties, length/time matching, post-route DRC settings, and debug layers — apply across the routing CLIs and are documented in full in [Configuration](docs/configuration.md).

## Requirements

- Python 3.9+ (the router is built `abi3-py39` whether it is downloaded or built
  from source, so building locally does not lower the floor — on 3.8 the module
  compiles and then fails to load with `symbol not found ... _PyCMethod_New`)
- numpy **1.22 or newer** (`pip3 install "numpy>=1.22"`) — below 1.22 the stack fails
  with errors that name neither numpy nor this tool: scipy's "A NumPy version
  >=1.22.4 ... is required" and `TypeError: 'numpy._DTypeMeta' object is not
  subscriptable`
- scipy (`pip3 install scipy`) - used for optimal target assignment and Voronoi partitioning
- shapely (`pip3 install shapely`) - used for polygon union in multi-net plane layers
- Rust toolchain — only needed if you build the router from source (`python build_router.py --from-source`); not required when using the prebuilt binary

## Limitations

- No push-and-shove (routes around obstacles, doesn't move them)
- No blind or buried vias
- No coarse grid assignment before detailed routing to plan overall topology
- No design rules by region/area support

## Contributing

The most valuable contribution is routing a board we haven't seen: run
`/plan-pcb-routing` on your own design (or any open-hardware board), grade
the result with `check_drc.py` + `check_connected.py`, and file an issue for
anything that breaks — ideally with a pointer to the board file. Fixes and
pull requests for open issues are just as welcome. See
[CONTRIBUTING.md](CONTRIBUTING.md) for the full guide.

## Support

KiCadRoutingTools is free and MIT-licensed, and it stays that way — there is no
paid tier, no feature held back, and nothing in this repository is paywalled.

Donations go to what it costs to build and maintain it: about **$500/month** of
cloud computing and AI-assisted development.

The compute is not incidental. Every change to the router is A/B-tested by
replaying a corpus of real open-source boards on rented cores and grading each
one for DRC violations and unconnected nets, and the ~600-file test suite fans
out the same way. It is what stops a change that helps one board from quietly
breaking ten others.

**[☕ Donate on Ko-fi](https://ko-fi.com/drandyhaas)** — card or PayPal, no account needed.
Prefer PayPal directly? **[paypal.me/DrAndyHaas](https://www.paypal.me/DrAndyHaas)** (the sender needs a PayPal account).

A donation buys no priority support and unlocks no features. If you would rather
contribute something worth more than money, route one of your own boards and file
an issue for whatever breaks — see [Contributing](#contributing).

## License

MIT License

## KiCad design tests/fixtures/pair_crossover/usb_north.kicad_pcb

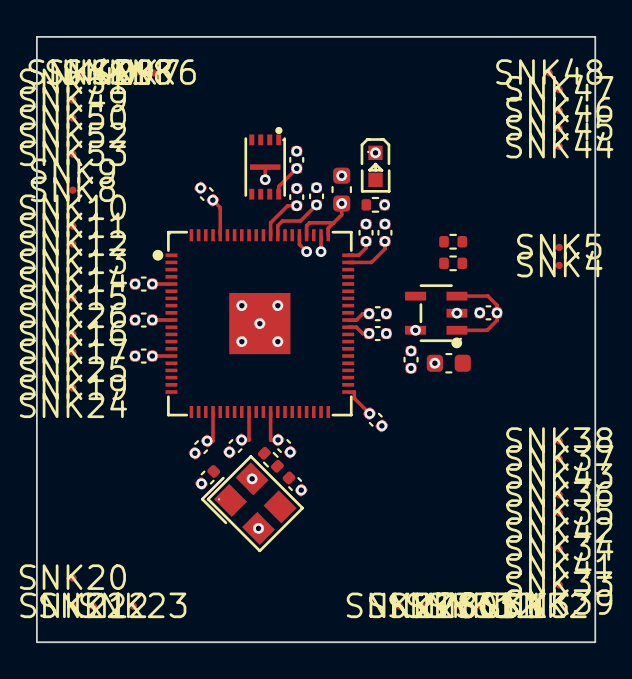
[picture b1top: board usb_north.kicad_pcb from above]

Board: 2 copper layers, 31.0 x 33.6 mm, 83 parts (0 on the bottom side), 68 nets.

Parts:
C1, C2, C3, C4, C5, C6, C7, C8, C9, C10, C11, C12, C13, C16, C17: GCM155R71H104KE02D; C_0402_1005Metric
C14, C15: CL05A105KP5NNNC; C_0402_1005Metric
C18, C19: JMK107C6475MA-T; C_0603_1608Metric
C20, C21: GCM1555C1H150FA16D; C_0402_1005Metric
D1: KT-0603G; LED0603-RD_C12624
R1: ERJ-2RKF4700X; R_0402_1005Metric
R2, R3: ERJ-2RKF27R0X; R_0402_1005Metric
R4: ERJ-2RKF1001X; R_0402_1005Metric
SNK1, SNK2, SNK3, SNK4, SNK5, SNK6, SNK7, SNK8, SNK9, SNK10, SNK11, SNK12, SNK13, SNK14, SNK15, SNK16, SNK17, SNK18, SNK19, SNK20, SNK21, SNK22, SNK23, SNK24, SNK25, SNK26, SNK27, SNK28, SNK29, SNK30, SNK31, SNK32, SNK33, SNK34, SNK35, SNK36, SNK37, SNK38, SNK39, SNK40, SNK41, SNK42, SNK43, SNK44, SNK45, SNK46, SNK47, SNK48, SNK49, SNK50, SNK51, SNK52, SNK53: sink
U1: W25Q16JVUXIQ; USON-8_L3.0-W2.0-P0.50-BL-EP
U2: RP2350B; QFN-80_L10.0-W10.0-P0.40-TL-EP3.4
U3: TLV74311PDBVR; SOT-23-5_L3.0-W1.7-P0.95-LS2.8-BL
Y1: ABM8-272-T3; CRYSTAL-SMD_4P-L3.2-W2.5-BL

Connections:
LED_PWR_NODE: D1.2, R1.2
OSC_XIN: C20.1, U2.30, Y1.1
OSC_XOUT: R4.2, U2.31
OSC_Y_XOUT: C21.1, R4.1, Y1.3
QSPI_SCLK: U1.6, U2.71
QSPI_SD0: U1.5, U2.72
QSPI_SD1: U1.2, U2.74
QSPI_SD2: U1.3, U2.73
QSPI_SD3: U1.7, U2.70
QSPI_SS: U1.1, U2.75
RUN: SNK1.1, U2.35
SWCLK: SNK2.1, U2.33
SWDIO: SNK3.1, U2.34
USB_MCU_N: R2.1, U2.66
USB_MCU_P: R3.1, U2.67
USB_N: R2.2, SNK4.1
USB_P: R3.2, SNK5.1
V1V1: C2.1, C3.1, C4.1, C15.1, C18.1, U2.10, U2.32, U2.51, U3.5
gnd: C1.2, C2.2, C3.2, C4.2, C5.2, C6.2, C7.2, C8.2, C9.2, C10.2, C11.2, C12.2, C13.2, C14.2, C15.2, C16.2, C17.2, C18.2, C19.2, C20.2, C21.2, D1.1, U1.4, U1.9, U2.62, U2.65, U2.81, U3.2, Y1.2, Y1.4
gpio0: SNK6.1, U2.77
gpio1: SNK7.1, U2.78
gpio2: SNK18.1, U2.79
gpio3: SNK29.1, U2.80
gpio4: SNK40.1, U2.1
gpio5: SNK49.1, U2.2
gpio6: SNK50.1, U2.3
gpio7: SNK51.1, U2.4
gpio8: SNK52.1, U2.6
gpio9: SNK53.1, U2.7
gpio10: SNK8.1, U2.8
gpio11: SNK9.1, U2.9
gpio12: SNK10.1, U2.11
gpio13: SNK11.1, U2.12
gpio14: SNK12.1, U2.13
gpio15: SNK13.1, U2.14
gpio16: SNK14.1, U2.16
gpio17: SNK15.1, U2.17
gpio18: SNK16.1, U2.18
gpio19: SNK17.1, U2.19
gpio20: SNK19.1, U2.20
gpio21: SNK20.1, U2.21
gpio22: SNK21.1, U2.22
gpio23: SNK22.1, U2.23
gpio24: SNK23.1, U2.25
gpio25: SNK24.1, U2.26
gpio26: SNK25.1, U2.27
gpio27: SNK26.1, U2.28
gpio28: SNK27.1, U2.36
gpio29: SNK28.1, U2.37
gpio30: SNK30.1, U2.38
gpio31: SNK31.1, U2.39
gpio32: SNK32.1, U2.40
gpio33: SNK33.1, U2.42
gpio34: SNK34.1, U2.43
gpio35: SNK35.1, U2.44
gpio36: SNK36.1, U2.45
gpio37: SNK37.1, U2.46
gpio38: SNK38.1, U2.47
gpio39: SNK39.1, U2.48
gpio40_adc0: SNK41.1, U2.49
gpio41_adc1: SNK42.1, U2.52
gpio42_adc2: SNK43.1, U2.53
gpio43_adc3: SNK44.1, U2.54
gpio44_adc4: SNK45.1, U2.55
gpio45_adc5: SNK46.1, U2.56
gpio46_adc6: SNK47.1, U2.57
gpio47_adc7: SNK48.1, U2.58
v3v3: C1.1, C5.1, C6.1, C7.1, C8.1, C9.1, C10.1, C11.1, C12.1, C13.1, C14.1, C16.1, C17.1, C19.1, R1.1, U1.8, U2.5, U2.15, U2.24, U2.29, U2.41, U2.50, U2.59, U2.60, U2.61, U2.64, U2.68, U2.69, U2.76, U3.1, U3.3
